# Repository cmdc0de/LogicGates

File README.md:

# LogicGates
simple boards to show using bcts or mosfets you can create logic gates

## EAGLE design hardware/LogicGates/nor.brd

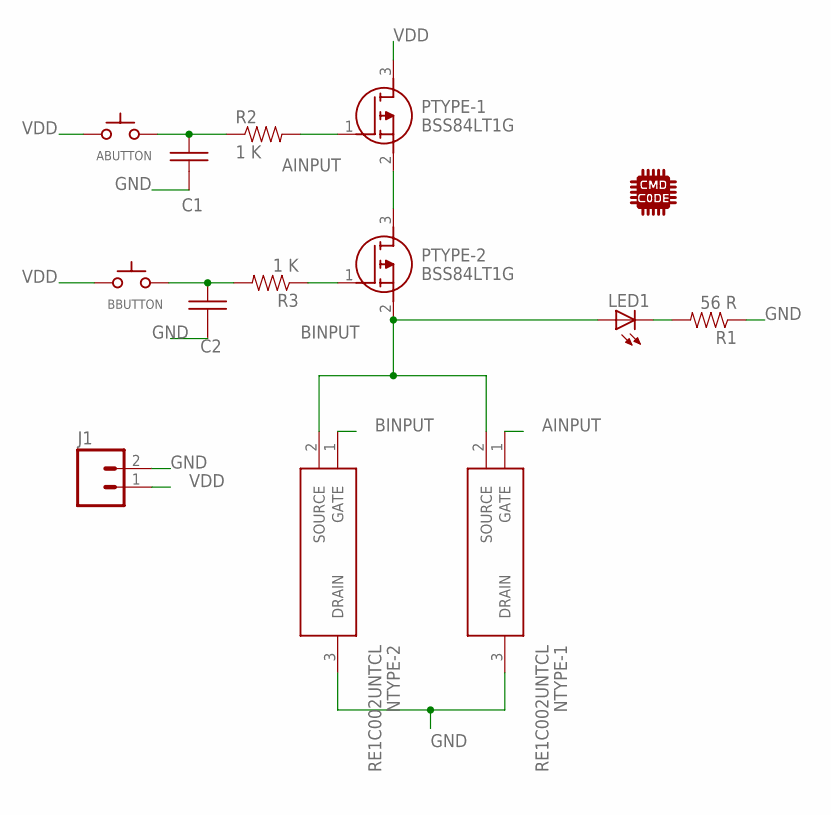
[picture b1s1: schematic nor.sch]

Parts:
ABUTTON: SWITCH_TACTILETACTILE-2PIN-NARROW; TACTILE-2PIN-NARROW
BBUTTON: SWITCH_TACTILETACTILE-2PIN-NARROW; TACTILE-2PIN-NARROW
C1, C2: C-USC1206; C1206
J1: M021X02_NO_SILK; 1X02_NO_SILK
LED1: LED3MM
NTYPE-1, NTYPE-2: RE1C002UNTCL; SOT50P160X85-3N
PTYPE-1, PTYPE-2: BSS84LT1G; SOT96P237X111-3N
R1: 56 R; 1206
R2, R3: 1 K; 0805
U$1: CMD_C0DE_LOGOCMD_CODE_LOGO_TOP_COPPER; CMD_C0DE_LOGO_TOP_COPPER

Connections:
AINPUT: NTYPE-1.1 (GATE), PTYPE-1.1 (G), R2.2
BINPUT: NTYPE-2.1 (GATE), PTYPE-2.1 (G), R3.1
GND: C1.2, C2.2, J1.2, NTYPE-1.3 (DRAIN), NTYPE-2.3 (DRAIN), R1.1
unnamed: ABUTTON.P$1 (A), C1.1, R2.1
unnamed: PTYPE-1.2 (S), PTYPE-2.3 (D)
unnamed: LED1.A, NTYPE-1.2 (SOURCE), NTYPE-2.2 (SOURCE), PTYPE-2.2 (S)
unnamed: LED1.K (C), R1.2
unnamed: BBUTTON.P$1 (A), C2.1, R3.2
VDD: ABUTTON.P$2 (C), BBUTTON.P$2 (C), J1.1, PTYPE-1.3 (D)

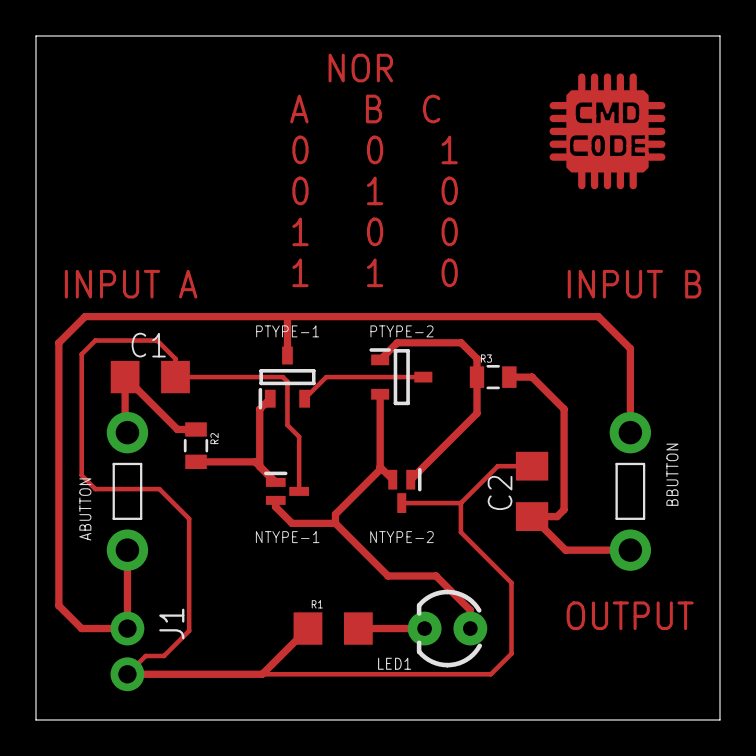
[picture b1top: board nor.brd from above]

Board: 2 copper layers, 38.0 x 38.0 mm, 14 parts (0 on the bottom side), 9 nets.

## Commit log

2019-09-03 initial nand example
2019-09-03 adding logo
2019-09-03 made truth table a device
2019-09-03 try again
2019-09-08 make it bigger
2019-09-09 nor gates added
